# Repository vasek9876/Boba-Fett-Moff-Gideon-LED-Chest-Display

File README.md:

# Boba-Fett-Moff-Gideon-LED-Chest-Display

Boba Fett / Moff Gideon LED Chest Display for cosplay or props.

This product is inspired by these [commercially accessible solution](https://www.etsy.com/au/listing/1456479470/high-quality-boba-fettmoff-gideon-led) - but made for a smaller chestplate
Function implemented to emulate the same functions as in this image - The current version of the code does not implement the last display function.

## Solution

- Multiplexed LED bar display for chest armor effects
- Gradual power-up sequence to detect brownout correctly
- Battery voltage monitoring with low-voltage deep sleep and green LED alert

## Usage
- Power the device with a suitable battery (9 V battery or use a 5–10 V battery, but a 5-18 V battery is suitable)
- LEDs gradually light up on startup when turned ON
- If battery voltage is too low, the circuit enters deep sleep and indicates the error with the green LED and "E" on the first segment display.
- It is possible to connect the powerbank directly to the pins used for the 9 V battery, but the consumption of the circuit is approximately 100 mA, so the circuit is not ready to run on a powerbank continuously (the powerbank turns off after a time because of its internal protection circuit)
  - Some old power banks are ready to be used with this device, but it is not guaranteed.
  - You can use, for example, this device [keep-alive device](https://www.sotabeams.co.uk/usb-battery-pack-keep-alive-load/) for the current version of the device.
- By the calculation, the 9 V battery should keep the device on for 3 - 5 hours, but it depends on the battery capacity and the battery's internal resistance.

## Programming
- Microcontroller: **ATmega328PB**
- Programming via **USB-ASP** device
- Use [AVRDUDE](https://github.com/avrdudes/avrdude) for direct programming; select "USBasp (USBasp ISP and TPI programmer)"
- Fuse settings for this project:
  - Low: `0xE2`
  - High: `0xD9`
  - Extended: `0xFD`
  - Lock Bits: `0xFF`
  - Verify fuses with [Engbedded Fuse Calculator](https://www.engbedded.com/fusecalc/)

- Firmware source code is included in [SW](https://github.com/vasek9876/Boba-Fett-Moff-Gideon-LED-Chest-Display/tree/all/sw)

## Notes

- Ensure proper power supply to avoid brownout during startup (>5 V)
- Multiplexing is handled in firmware
- The rapid switching of LEDs may generate audible noise from the power supply or nearby components; this is normal and does not indicate a fault.

## Goal and further developement

- The goal of this open hw is to make this relatively simple custom device based on AtMega accessible for anyone.
- The current development is stopped, but there are known issues, which will be resolved in a few months.

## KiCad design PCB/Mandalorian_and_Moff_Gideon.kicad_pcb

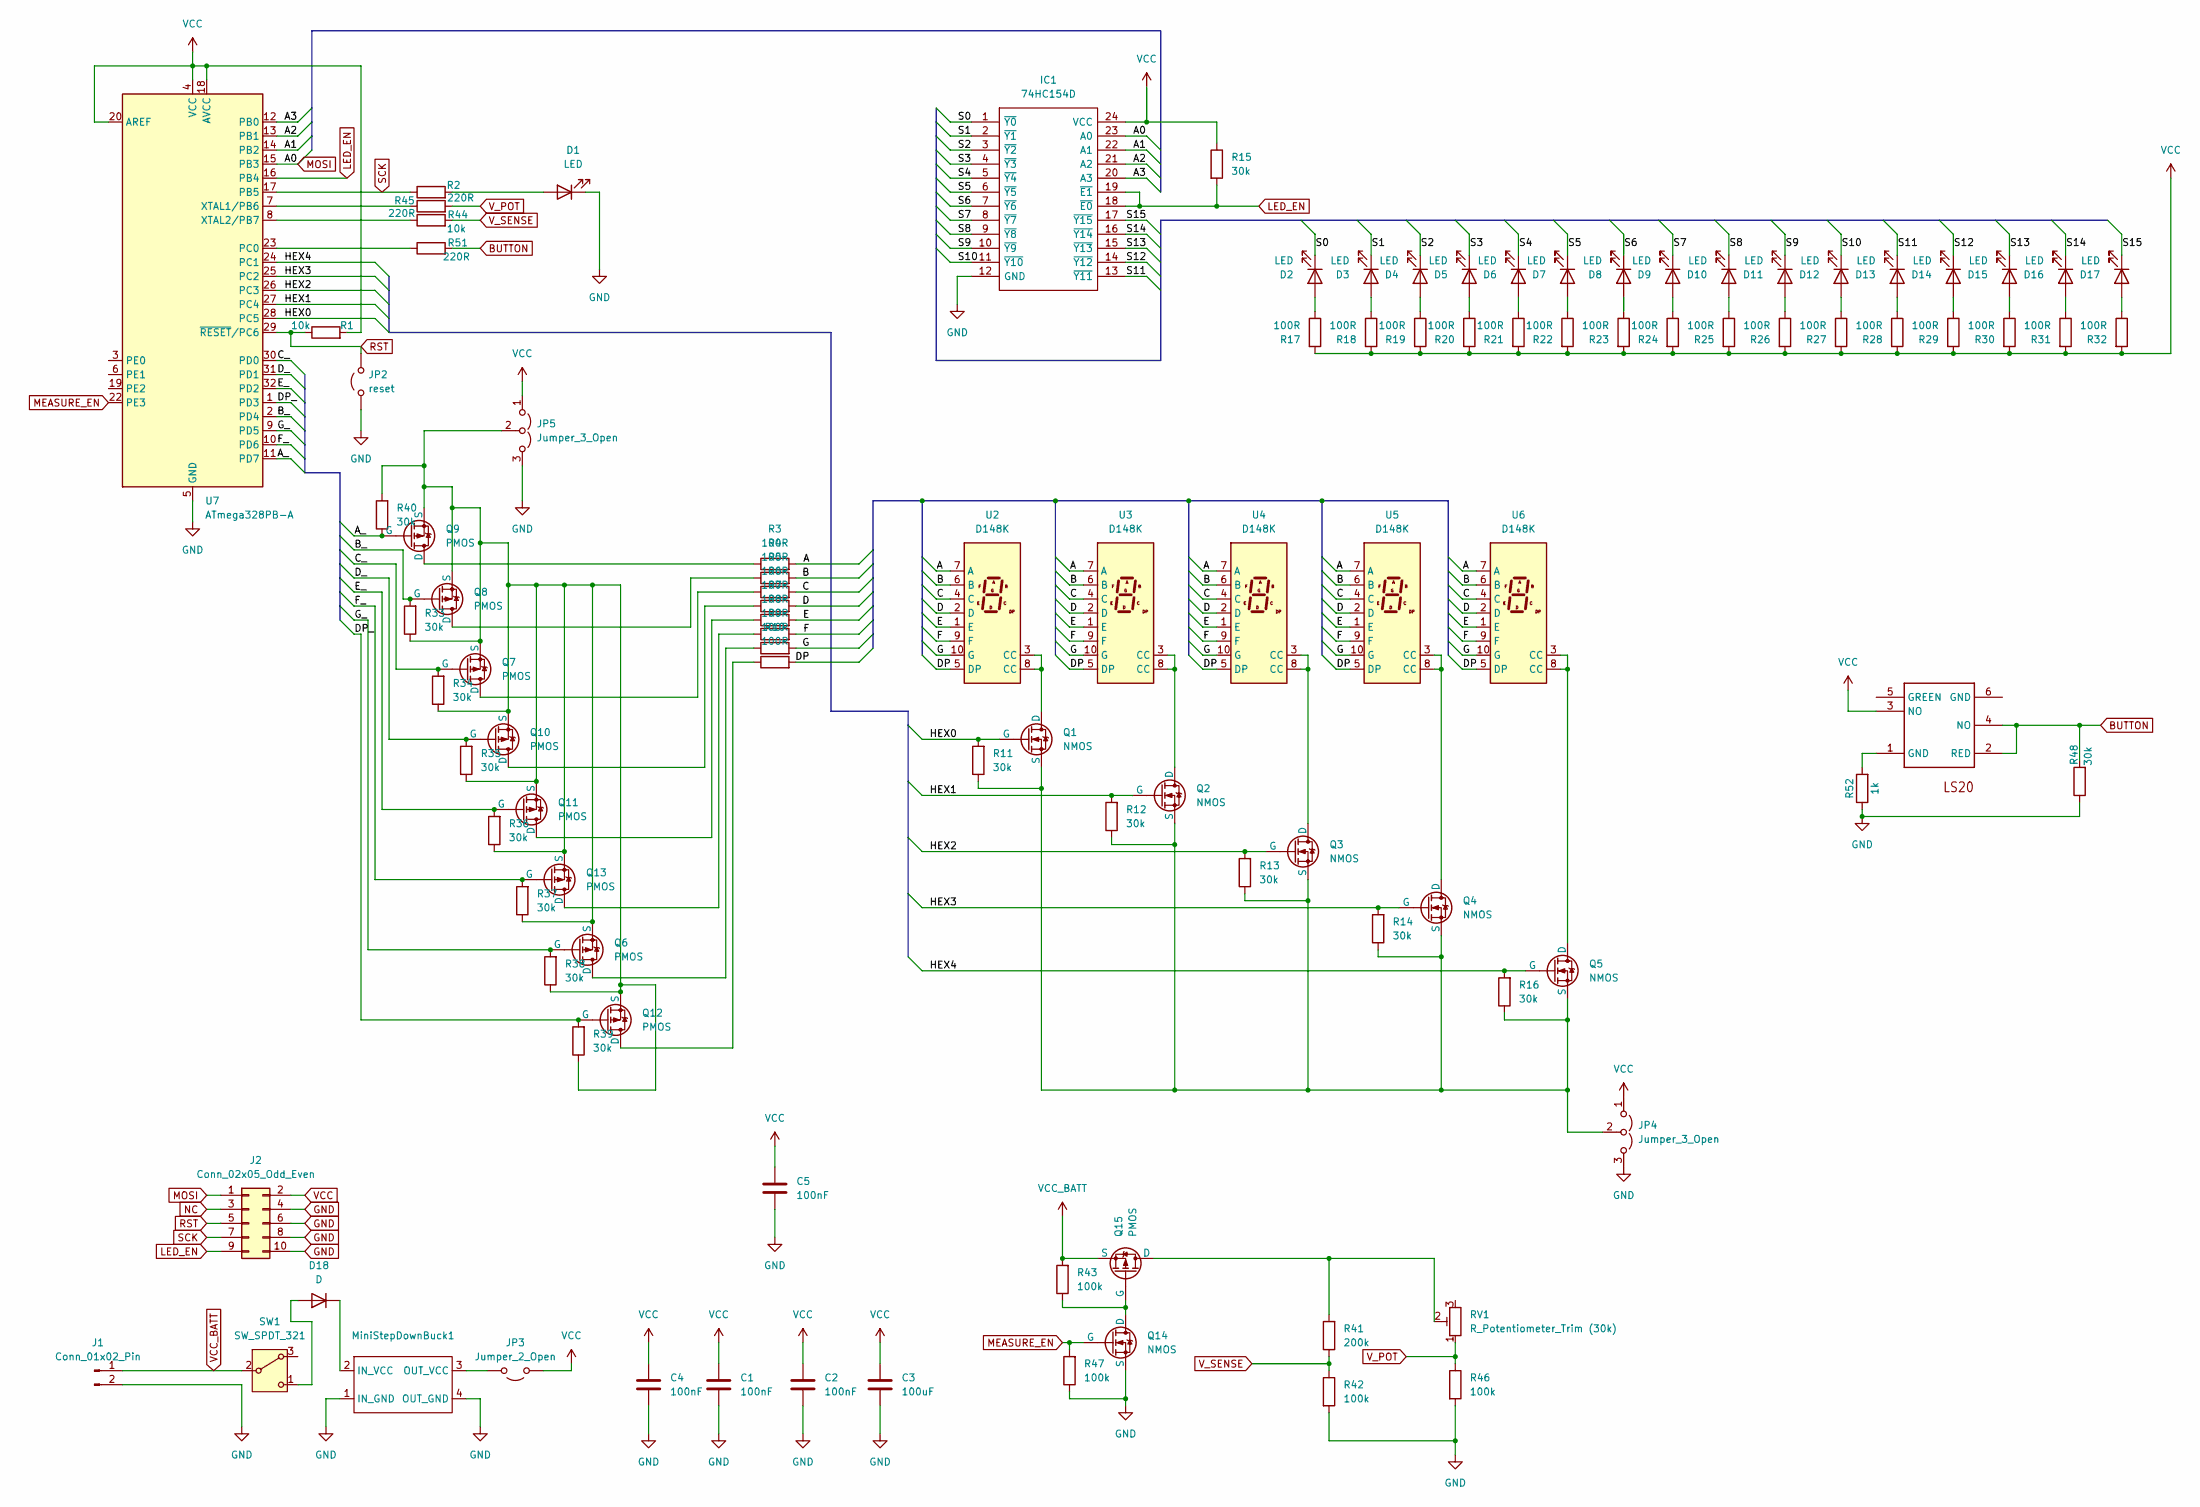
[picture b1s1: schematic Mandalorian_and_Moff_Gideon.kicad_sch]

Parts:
C1, C2, C4, C5: 100nF; C_0805_2012Metric
C3: 100uF; CP_Radial_D4.0mm_P2.00mm
D1: LED; LED_0603_1608Metric
D2, D3, D4, D5, D6, D7, D8, D9, D10, D11, D12, D13, D14, D15, D16, D17: LED; LED_0805_2012Metric
D18: D; D_DO-15_P12.70mm_Horizontal
IC1: 74HC154D; SOIC127P1032X265-24N; Manufacturer_Part_Number 74HC154D; Mouser Part Number 771-74HC154D
J1: Conn_01x02_Pin; PinHeader_1x02_P2.54mm_Horizontal
J2: Conn_02x05_Odd_Even; PinHeader_2x05_P2.54mm_Horizontal
JP2: reset; SolderJumper-2_P1.3mm_Open_RoundedPad1.0x1.5mm
JP3: Jumper_2_Open; PinHeader_1x02_P2.54mm_Horizontal
JP4, JP5: Jumper_3_Open; SolderJumper-3_P1.3mm_Open_RoundedPad1.0x1.5mm
LS20: LS20
MiniStepDownBuck1: Step_down_360
Q1, Q2, Q3, Q4, Q5, Q14: NMOS; SOT-23
Q6, Q7, Q8, Q9, Q10, Q11, Q12, Q13, Q15: PMOS; SOT-23
R1, R44: 10k; R_0805_2012Metric
R2, R45, R51: 220R; R_0805_2012Metric
R3, R4, R5, R6, R7, R8, R9, R10, R17, R18, R19, R20, R21, R22, R23, R24, R25, R26, R27, R28, R29, R30, R31, R32: 100R; R_0805_2012Metric
R11, R12, R13, R14, R15, R16, R33, R34, R35, R36, R37, R38, R39, R40, R48: 30k; R_0805_2012Metric
R41: 200k; R_0805_2012Metric
R42, R43, R46, R47: 100k; R_0805_2012Metric
R52: 1k; R_0805_2012Metric
RV1: R_Potentiometer_Trim (30k); Potentiometer_Runtron_RM-065_Vertical
SW1: SW_SPDT_321; PinHeader_1x03_P2.54mm_Horizontal
U2, U3, U4, U5, U6: D148K; 157112B12700
U7: ATmega328PB-A; TQFP-32_7x7mm_P0.8mm

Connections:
/A: R3.2, U2.7 (A), U3.7 (A), U4.7 (A), U5.7 (A), U6.7 (A)
/A1: IC1.22 (A1), U7.14 (PB2)
/A2: IC1.21 (A2), U7.13 (PB1)
/A3: IC1.20 (A3), U7.12 (PB0)
/A_: Q9.1 (G), R40.1, U7.11 (PD7)
/B: R4.2, U2.6 (B), U3.6 (B), U4.6 (B), U5.6 (B), U6.6 (B)
/B_: Q8.1 (G), R33.2, U7.2 (PD4)
/C: R5.2, U2.4 (C), U3.4 (C), U4.4 (C), U5.4 (C), U6.4 (C)
/C_: Q7.1 (G), R34.2, U7.30 (PD0)
/D: R6.2, U2.2 (D), U3.2 (D), U4.2 (D), U5.2 (D), U6.2 (D)
/DP: R10.2, U2.5 (DP), U3.5 (DP), U4.5 (DP), U5.5 (DP), U6.5 (DP)
/DP_: Q12.1 (G), R39.2, U7.1 (PD3)
/D_: Q10.1 (G), R35.2, U7.31 (PD1)
/E: R7.2, U2.1 (E), U3.1 (E), U4.1 (E), U5.1 (E), U6.1 (E)
/E_: Q11.1 (G), R36.2, U7.32 (PD2)
/F: R8.2, U2.9 (F), U3.9 (F), U4.9 (F), U5.9 (F), U6.9 (F)
/F_: Q13.1 (G), R37.2, U7.10 (PD6)
/G: R9.2, U2.10 (G), U3.10 (G), U4.10 (G), U5.10 (G), U6.10 (G)
/G_: Q6.1 (G), R38.2, U7.9 (PD5)
/HEX0: Q1.1 (G), R11.2, U7.28 (PC5)
/HEX1: Q2.1 (G), R12.2, U7.27 (PC4)
/HEX2: Q3.1 (G), R13.2, U7.26 (PC3)
/HEX3: Q4.1 (G), R14.2, U7.25 (PC2)
/HEX4: Q5.1 (G), R16.2, U7.24 (PC1)
/S0: D2.1 (K), IC1.1 (~Y0)
/S1: D3.1 (K), IC1.2 (~Y1)
/S2: D4.1 (K), IC1.3 (~Y2)
/S3: D5.1 (K), IC1.4 (~Y3)
/S4: D6.1 (K), IC1.5 (~Y4)
/S5: D7.1 (K), IC1.6 (~Y5)
/S6: D8.1 (K), IC1.7 (~Y6)
/S7: D9.1 (K), IC1.8 (~Y7)
/S8: D10.1 (K), IC1.9 (~Y8)
/S9: D11.1 (K), IC1.10 (~Y9)
/S10: D12.1 (K), IC1.11 (~Y10)
/S11: D13.1 (K), IC1.13 (~Y11)
/S12: D14.1 (K), IC1.14 (~Y12)
/S13: D15.1 (K), IC1.15 (~Y13)
/S14: D16.1 (K), IC1.16 (~Y14)
/S15: D17.1 (K), IC1.17 (~Y15)
BUTTON: LS20.2 (RED), LS20.4 (NO), R48.2, R51.2
GND: C1.2, C2.2, C3.2, C4.2, C5.2, D1.1 (K), IC1.12 (GND), J1.2, J2.4, J2.6, J2.8, J2.10, JP2.1 (A), JP4.3 (B), JP5.3 (B), MiniStepDownBuck1.1 (IN_GND), MiniStepDownBuck1.4 (OUT_GND), Q14.2 (S), R42.2, R46.2, R47.1, R48.1, R52.1, U7.5 (GND), U7.21 (GND)
LED_EN: IC1.18 (~E0), IC1.19 (~E1), J2.9, R15.2, U7.16 (PB4)
MEASURE_EN: Q14.1 (G), R47.2, U7.22 (PE3)
MOSI: IC1.23 (A0), J2.1, U7.15 (PB3)
NC: J2.3
unnamed: D1.2 (A), R2.2
unnamed: D2.2 (A), R17.1
unnamed: D3.2 (A), R18.1
unnamed: D4.2 (A), R19.1
unnamed: D5.2 (A), R20.1
unnamed: D6.2 (A), R21.1
unnamed: D7.2 (A), R22.1
unnamed: D8.2 (A), R23.1
unnamed: D9.2 (A), R24.1
unnamed: D10.2 (A), R25.1
unnamed: D11.2 (A), R26.1
unnamed: D12.2 (A), R27.1
unnamed: D13.2 (A), R28.1
unnamed: D14.2 (A), R29.1
unnamed: D15.2 (A), R30.1
unnamed: D16.2 (A), R31.1
unnamed: D17.2 (A), R32.1
unnamed: D18.2 (A), SW1.1 (C)
unnamed: D18.1 (K), MiniStepDownBuck1.2 (IN_VCC)
unnamed: JP3.2 (B), MiniStepDownBuck1.3 (OUT_VCC)
unnamed: JP4.2 (C), Q1.2 (S), Q2.2 (S), Q3.2 (S), Q4.2 (S), Q5.2 (S), R11.1, R12.1, R13.1, R14.1, R16.1
unnamed: JP5.2 (C), Q6.2 (S), Q7.2 (S), Q8.2 (S), Q9.2 (S), Q10.2 (S), Q11.2 (S), Q12.2 (S), Q13.2 (S), R33.1, R34.1, R35.1, R36.1, R37.1, R38.1, R39.1, R40.2
unnamed: LS20.1 (GND), R52.2
unnamed: Q1.3 (D), U2.3 (CC), U2.8 (CC)
unnamed: Q2.3 (D), U3.3 (CC), U3.8 (CC)
unnamed: Q3.3 (D), U4.3 (CC), U4.8 (CC)
unnamed: Q4.3 (D), U5.3 (CC), U5.8 (CC)
unnamed: Q5.3 (D), U6.3 (CC), U6.8 (CC)
unnamed: Q6.3 (D), R9.1
unnamed: Q7.3 (D), R5.1
unnamed: Q8.3 (D), R4.1
unnamed: Q9.3 (D), R3.1
unnamed: Q10.3 (D), R6.1
unnamed: Q11.3 (D), R7.1
unnamed: Q12.3 (D), R10.1
unnamed: Q13.3 (D), R8.1
unnamed: Q14.3 (D), Q15.1 (G), R43.1
unnamed: Q15.3 (D), R41.2, RV1.2
unnamed: R51.1, U7.23 (PC0)
unnamed: R45.1, U7.7 (XTAL1/PB6)
unnamed: R44.1, U7.8 (XTAL2/PB7)
RST: J2.5, JP2.2 (B), R1.1, U7.29 (~RESET/PC6)
SCK: J2.7, R2.1, U7.17 (PB5)
VCC: C1.1, C2.1, C3.1, C4.1, C5.1, IC1.24 (VCC), J2.2, JP3.1 (A), JP4.1 (A), JP5.1 (A), LS20.3 (NO), R1.2, R15.1, R17.2, R18.2, R19.2, R20.2, R21.2, R22.2, R23.2, R24.2, R25.2, R26.2, R27.2, R28.2, R29.2, R30.2, R31.2, R32.2, U7.4 (VCC), U7.18 (AVCC), U7.20 (AREF)
VCC_BATT: J1.1, Q15.2 (S), R43.2, SW1.2 (B)
V_POT: R45.2, R46.1, RV1.1
V_SENSE: R41.1, R42.1, R44.2

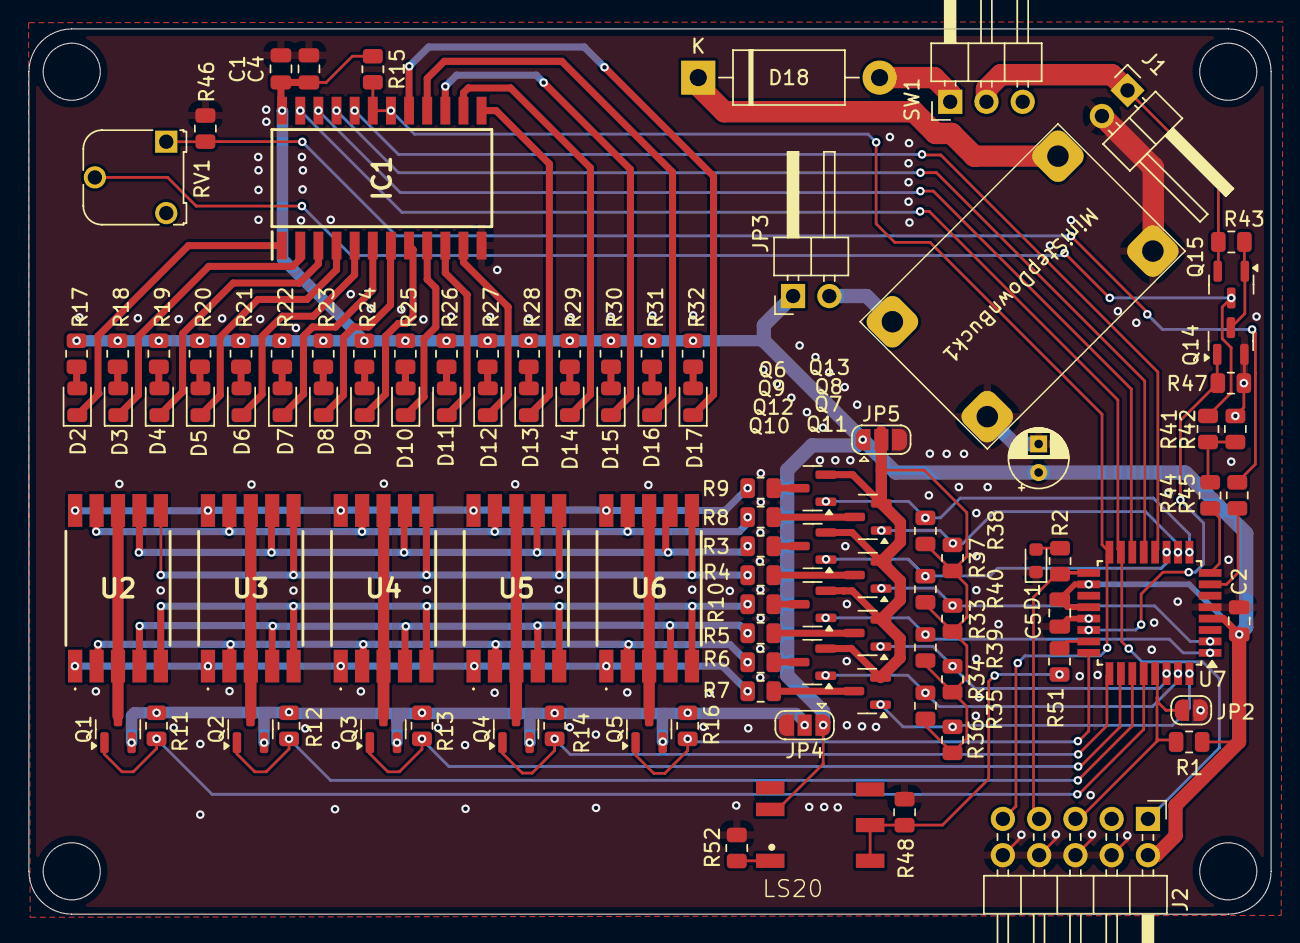
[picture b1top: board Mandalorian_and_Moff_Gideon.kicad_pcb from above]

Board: 2 copper layers, 87.0 x 62.0 mm, 105 parts (0 on the bottom side), 92 nets.

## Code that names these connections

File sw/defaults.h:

#ifndef defaults_h
#define defaults_h

#include <avr/io.h>

#ifdef OLD

// 88888
#define PATTERN_51 0b11101111
#define PATTERN_52 0b11101111
#define PATTERN_53 0b11101111
#define PATTERN_54 0b11101111
#define PATTERN_55 0b11101111

// DUEPI
#define PATTERN_21 0b00000010
#define PATTERN_22 0b10001111
#define PATTERN_23 0b11000111
#define PATTERN_24 0b11101010
#define PATTERN_25 0b11101001

// AEAOE
#define PATTERN_11 0b10000011
#define PATTERN_12 0b11101100
#define PATTERN_13 0b10101101
#define PATTERN_14 0b11000111
#define PATTERN_15 0b10100111

// caj
#define PATTERN_41 0b00000101
#define PATTERN_42 0b10000010
#define PATTERN_43 0b01000100
#define PATTERN_44 0b00100010
#define PATTERN_45 0b00001001

// DUEPI again

// H5291
#define PATTERN_31 0b10000010
#define PATTERN_32 0b00101111
#define PATTERN_33 0b11001101
#define PATTERN_34 0b01100011
#define PATTERN_35 0b10101011

#else

// 88888
#define PATTERN_51 0b00001000
#define PATTERN_52 0b00001000
#define PATTERN_53 0b00001000
#define PATTERN_54 0b00001000
#define PATTERN_55 0b00001000

// DUEPI
#define PATTERN_21 0b10111111
#define PATTERN_22 0b00001011
#define PATTERN_23 0b00011001
#define PATTERN_24 0b10101000
#define PATTERN_25 0b11001000

// AEAOE
#define PATTERN_11 0b10011011
#define PATTERN_12 0b01101000
#define PATTERN_13 0b01001010
#define PATTERN_14 0b00011001
#define PATTERN_15 0b00011010

// caj
#define PATTERN_41 0b01011111
#define PATTERN_42 0b10111011
#define PATTERN_43 0b01111101
#define PATTERN_44 0b10111110
#define PATTERN_45 0b11001111

// DUEPI again

// H5291
#define PATTERN_31 0b10111011
#define PATTERN_32 0b00001110
#define PATTERN_33 0b01001001
#define PATTERN_34 0b10011100
#define PATTERN_35 0b10001010

// now afgbhedc (default abcdefgh)

#define PATTERN_0 0b00101000  // 0 // OK
#define PATTERN_1 0b10111011  // 1 // OK
#define PATTERN_2 0b01001001  // 2 // OK
#define PATTERN_3 0b01001100  // 3 // OK
#define PATTERN_4 0b10001110  // 4 // OK
#define PATTERN_5 0b00011100  // 5
#define PATTERN_6 0b00011000  // 6
#define PATTERN_7 0b01101110  // 7
#define PATTERN_8 0b00001000  // 8
#define PATTERN_9 0b00001110  // 9
#define PATTERN_E 0b00011001  // E

#define PATTERN_0_DP 0b00100000  // 0 // OK
#define PATTERN_1_DP 0b10110011  // 1 // OK
#define PATTERN_2_DP 0b01000001  // 2 // OK
#define PATTERN_3_DP 0b01000100  // 3 // OK
#define PATTERN_4_DP 0b10000110  // 4 // OK
#define PATTERN_5_DP 0b00010100  // 5
#define PATTERN_6_DP 0b00010000  // 6
#define PATTERN_7_DP 0b01100110  // 7
#define PATTERN_8_DP 0b00000000  // 8
#define PATTERN_9_DP 0b00000110  // 9

#define PATTERN_U 0b10101000

#endif

#ifdef TEST



#define PATTERN_11 0b01111111
#define PATTERN_12 0b01110111
#define PATTERN_13 0b01111011
#define PATTERN_14 0b01111101
#define PATTERN_15 0b01111110

#endif

// in sec
#define REPEAT_FUNC1 27*2 // 0.49
#define REPEAT_FUNC2 28*2 // 0.51
#define REPEAT_FUNC3 26*2 // 0.48
#define REPEAT_FUNC4 40*2 // 0.72  
#define REPEAT_FUNC5 30*2 // 0.54
#define REPEAT_FUNC6 27*2 // 0.50

// digits

const byte DIGITS[10] = {
    PATTERN_0,
    PATTERN_1,
    PATTERN_2,
    PATTERN_3,
    PATTERN_4,
    PATTERN_5,
    PATTERN_6,
    PATTERN_7,
    PATTERN_8,
    PATTERN_9
};


const byte bar_map[16][4] = {
  // D, B, A, C (DCBA - 1111)
  {0,0,0,0},
  {0,0,1,0},
  {0,1,0,0},
  {0,1,1,0},
  {0,0,0,1},
  {0,0,1,1},
  {0,1,0,1},
  {0,1,1,1},

  {1,0,0,0},
  {1,0,1,0},
  {1,1,0,0},
  {1,1,1,0},
  {1,0,0,1},
  {1,0,1,1},
  {1,1,0,1},
  {1,1,1,1},
};

// Old
#ifdef OLD
const byte bar_map[16][4] = {
    {0,0,0,1},
    {0,1,0,0},
    {0,0,1,0},
    {0,0,0,0},
    {1,0,0,0},
    {1,1,0,0},
    {0,1,0,1},
    {1,1,0,1},
    {0,0,1,0},
    {1,0,1,0},
    {0,0,1,1},
    {1,0,1,1},
    {0,1,1,0},
    {1,1,1,0},
    {0,1,1,1},
    {1,1,1,1}
};
#endif



const byte pattern_numbers[] = {PATTERN_0, PATTERN_1, PATTERN_2, PATTERN_3, PATTERN_4,
                                PATTERN_5, PATTERN_6, PATTERN_7, PATTERN_8, PATTERN_9};

const byte pattern_numbers_DP[] = {PATTERN_0_DP, PATTERN_1_DP, PATTERN_2_DP, PATTERN_3_DP, PATTERN_4_DP,
                                PATTERN_5_DP, PATTERN_6_DP, PATTERN_7_DP, PATTERN_8_DP, PATTERN_9_DP};


const byte pattern1[] = {PATTERN_11, PATTERN_12, PATTERN_13, PATTERN_14, PATTERN_15};
const byte pattern2[] = {PATTERN_21, PATTERN_22, PATTERN_23, PATTERN_24, PATTERN_25};
const byte pattern3[] = {PATTERN_31, PATTERN_32, PATTERN_33, PATTERN_34, PATTERN_35};
const byte pattern4[] = {PATTERN_41, PATTERN_42, PATTERN_43, PATTERN_44, PATTERN_45};
const byte pattern5[] = {PATTERN_51, PATTERN_52, PATTERN_53, PATTERN_54, PATTERN_55};



// LED pin
#define LED_PIN PB5

// LCD segments on PORTC bits 5..1
// const int lcd_addr[] = { A5, A4, A3, A2, A1 };  // Segments: PC5,PC4,PC3,PC2,PC1
#define LCD_PORT PORTC
#define LCD_DDR DDRC
#define LCD_MASK ((1 << PC5) | (1 << PC4) | (1 << PC3) | (1 << PC2) | (1 << PC1))

#define NUM_SEG 5  // Number of LCD segments

// Bar LEDs on PORTB bits 0,2,3,1 (in that order)
// const int bar_leds[] = { 8, 10, 11, 9 };  // PB0, PB2, PB3, PB1
#define BAR_PORT PORTB
#define BAR_DDR DDRB
#define BAR_MASK ((1 << PB0) | (1 << PB2) | (1 << PB3) | (1 << PB1))

// map bits to actual PORTB bits
static const uint8_t barBits[4] = { (1 << PB0), (1 << PB2), (1 << PB3), (1 << PB1) };

// const int bar_leds_en = 12;  // PB4
#define BAR_EN_PORT PORTB
#define BAR_EN_DDR DDRB
#define BAR_EN_BIT PB4

#endif

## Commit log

2025-12-10 sw v1
2025-12-11 PCB
    kicad - PCB last version
    - badly routed V_BAT measurement and the analog pins - they are not at analog inputs
    - the reverse polarity protection is not ok with deiode - next iteration should have the ideal diode using Pmos
2025-12-11 Last firmware with loading and voltage indication
    - In the last firmware, the first step tries to turn on all bar LEDs gradually, which is necessary to slowly increase power consumption and check for brownout detection.
    - After the loading bar, the battery voltage is measured three times, typically ranging from about 5.000 V to 9.999 V. If the voltage is lower, the circuit enters deep sleep, and the green LED on the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
    - After these steps, the normal program starts running.
2025-12-11 hw - 3D model
